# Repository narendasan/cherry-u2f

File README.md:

# cherry-u2f
Based off of conorpp's u2f-zero project, creates a u2f key with a cherry mx switch

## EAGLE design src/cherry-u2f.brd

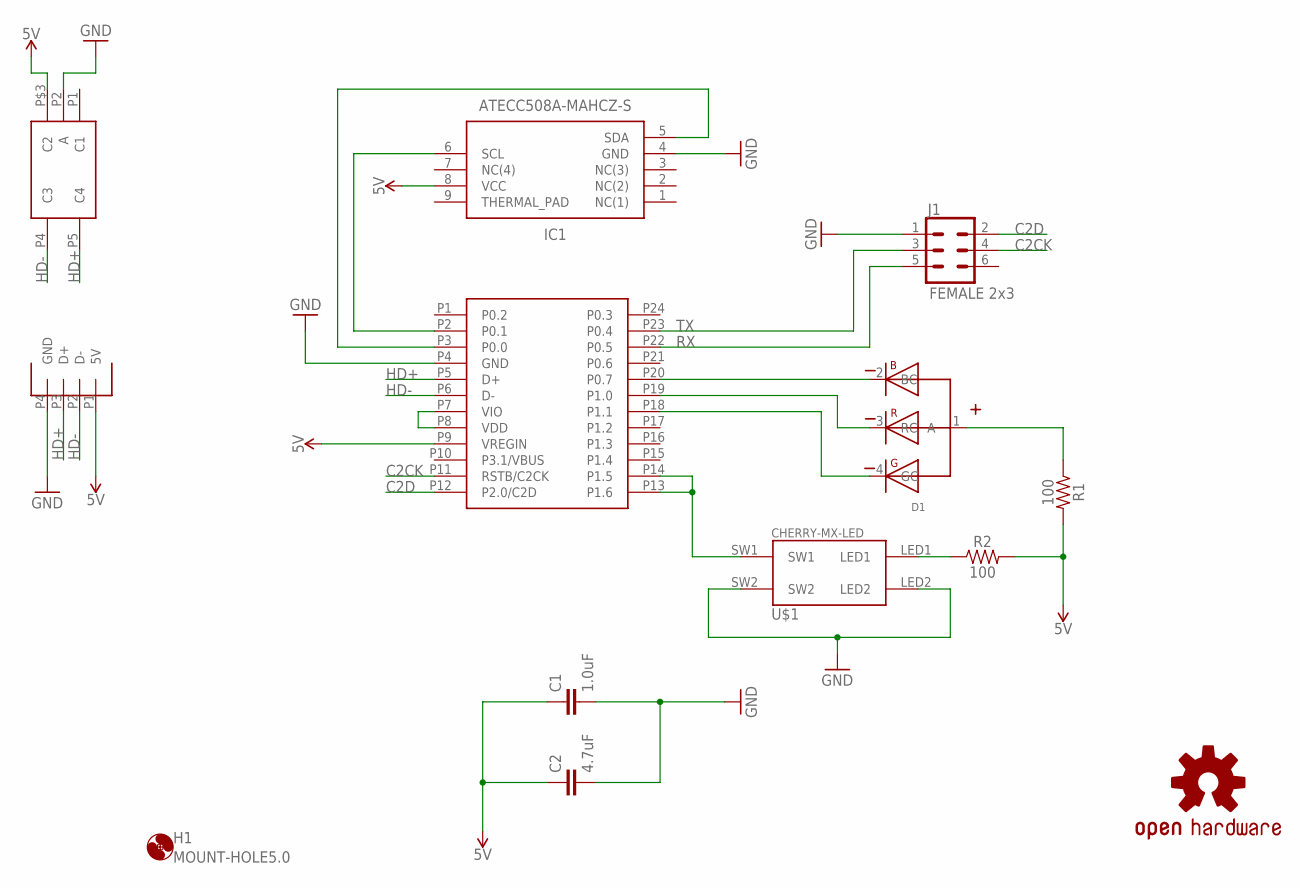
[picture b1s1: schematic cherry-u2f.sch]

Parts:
C1: 1.0uF; 0603
C2: 4.7uF; 0603
D1: WL-SFTW-150141M173100-R&G&B; WL-SFTW_3528
H1: MOUNT-HOLE5.0; 5,0
IC1: ATECC508A-MAHCZ-S; SON50P300X200X60-9N
J1: FEMALE 2x3; 2X3
LOGO1: OSHW-LOGOS; OSHW-LOGO-S
R1, R2: 100; 0603
U$1: CHERRY-MX-LED
U$2: EFM8UB1-QSOP24; QSOP24
U$3: DF5A5.6JE
U$4: USB-A-PCB

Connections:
5V: C1.1, C2.1, IC1.8 (VCC), R1.2, R2.2, U$2.P9 (VREGIN), U$3.P$3 (C2), U$4.P1 (5V)
C2CK: J1.4, U$2.P11 (RSTB/C2CK)
C2D: J1.2, U$2.P12 (P2.0/C2D)
GND: C1.2, C2.2, IC1.4 (GND), J1.1, U$1.LED2, U$1.SW2, U$2.P4 (GND), U$3.P2 (A), U$4.P4 (GND)
HD+: U$2.P5 (D+), U$3.P5 (C4), U$4.P3 (D+)
HD-: U$2.P6 (D-), U$3.P4 (C3), U$4.P2 (D-)
unnamed: U$1.SW1, U$2.P13 (P1.6), U$2.P14 (P1.5)
unnamed: U$2.P7 (VIO), U$2.P8 (VDD)
unnamed: R2.1, U$1.LED1
unnamed: D1.3 (RC), U$2.P19 (P1.0)
unnamed: D1.1 (A), R1.1
unnamed: D1.2 (BC), U$2.P20 (P0.7)
unnamed: D1.4 (GC), U$2.P18 (P1.1)
unnamed: IC1.6 (SCL), U$2.P2 (P0.1)
unnamed: IC1.5 (SDA), U$2.P3 (P0.0)
RX: J1.5, U$2.P22 (P0.5)
TX: J1.3, U$2.P23 (P0.4)

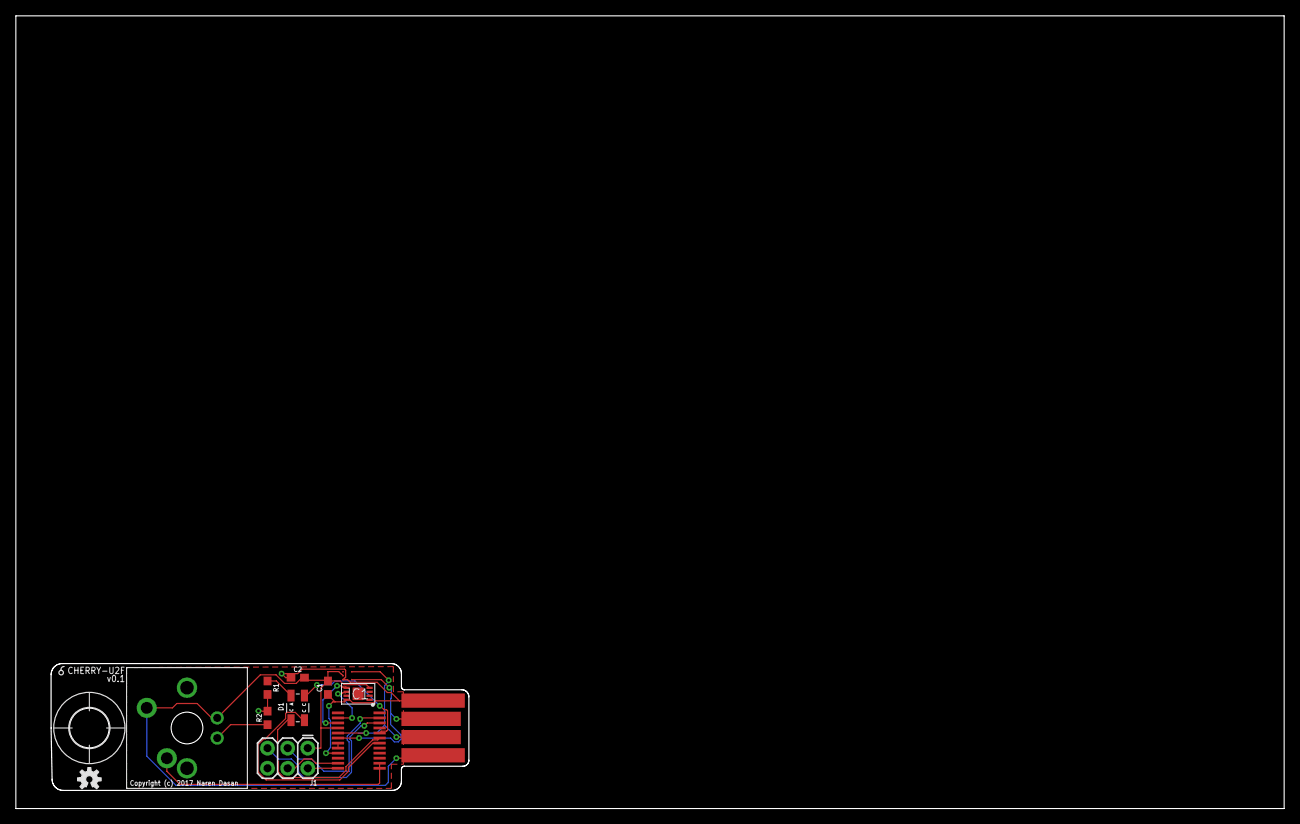
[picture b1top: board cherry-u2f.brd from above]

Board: 2 copper layers, 160.0 x 100.0 mm, 13 parts (0 on the bottom side), 17 nets.

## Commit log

2017-10-14 v0.1

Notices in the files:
src/cherry-u2f.brd:
Copyright (c) 2017 Naren Dasan
parts and their libraries:
SparkFun-Capacitors: Licensing: Creative Commons ShareAlike 4.0 International - https://creativecommons.org/licenses/by-sa/4.0
Wurth_Elektronik_Optoelectronics_rev17b: Copyright: Würth Elektronik
